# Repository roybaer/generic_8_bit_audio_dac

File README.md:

# Generic 8 bit audio DAC

These are KiCAD and Inkscape design files for a generic Covox Speech Thing compatible parallel port audio DAC.

This particular design uses a 100kΩ SIP R2R DAC with a 25.5kΩ load resistor and a pass-through connector for a printer and is therefore significantly closer to the original than most other imitations.

## Photo

## License

This work is licensed under the Creative Commons Attribution-ShareAlike 4.0 International License. To view a copy of this license, visit http://creativecommons.org/licenses/by-sa/4.0/ or send a letter to Creative Commons, PO Box 1866, Mountain View, CA 94042, USA.

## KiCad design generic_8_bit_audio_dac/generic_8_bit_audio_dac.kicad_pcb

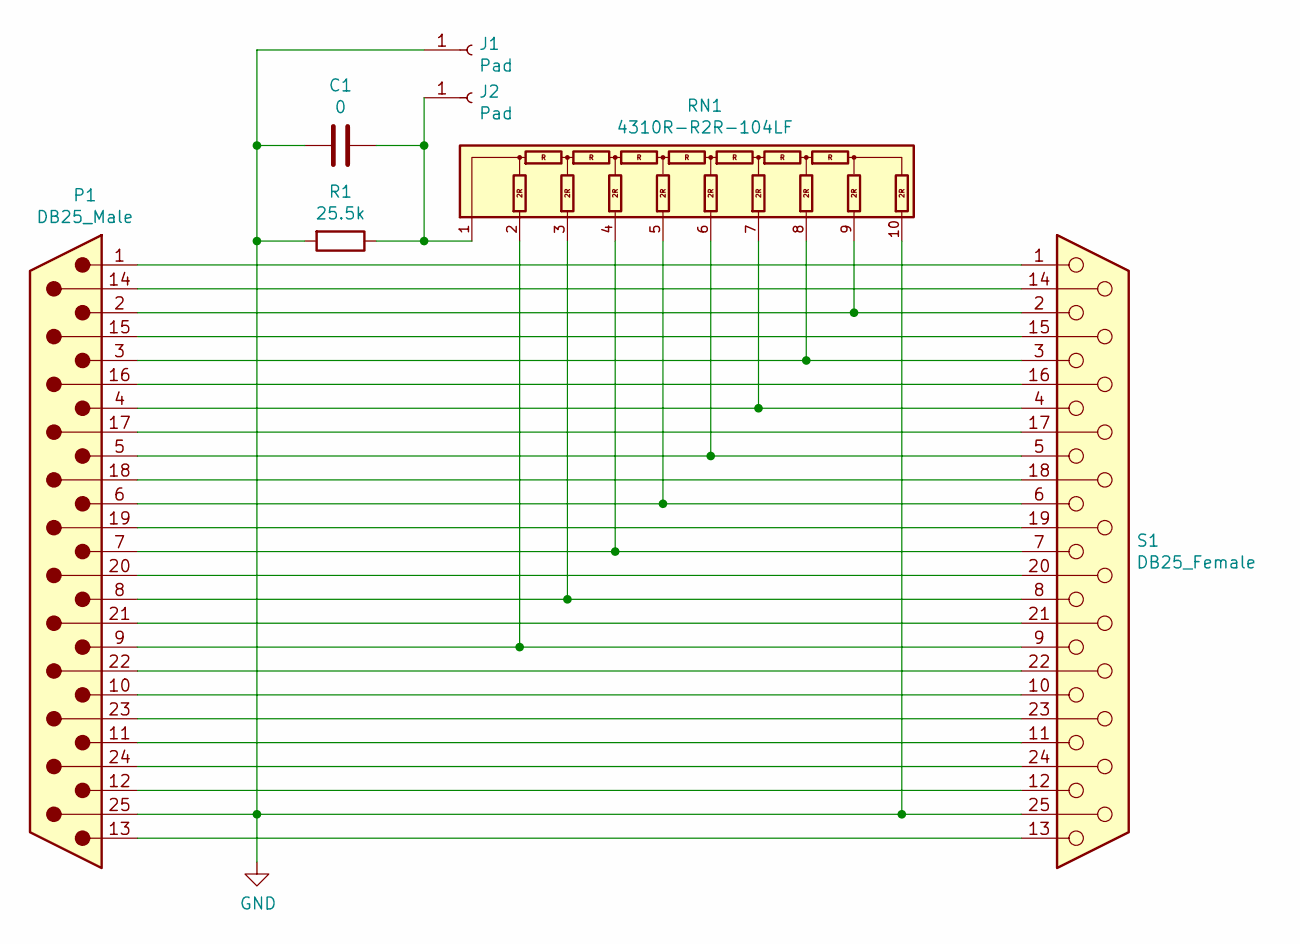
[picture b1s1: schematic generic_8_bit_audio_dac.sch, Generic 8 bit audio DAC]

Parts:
C1: 0; C_Disc_D4.7mm_W2.5mm_P5.00mm
J1, J2: Pad; SolderWirePad_1x01_Drill1.2mm
P1: DB25_Male; DSUB-25_Male_EdgeMount_P2.77mm
R1: 25.5k; R_Axial_DIN0309_L9.0mm_D3.2mm_P20.32mm_Horizontal
RN1: 4310R-R2R-104LF; R_Array_SIP10
S1: DB25_Female; DSUB-25_Female_EdgeMount_P2.77mm

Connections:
GND: C1.2, J1.1, P1.25, R1.2, RN1.10, S1.25
unnamed: C1.1, J2.1, R1.1, RN1.1
unnamed: P1.1, S1.1
unnamed: P1.2, RN1.9, S1.2
unnamed: P1.3, RN1.8, S1.3
unnamed: P1.4, RN1.7, S1.4
unnamed: P1.5, RN1.6, S1.5
unnamed: P1.6, RN1.5, S1.6
unnamed: P1.7, RN1.4, S1.7
unnamed: P1.8, RN1.3, S1.8
unnamed: P1.9, RN1.2, S1.9
unnamed: P1.10, S1.10
unnamed: P1.11, S1.11
unnamed: P1.12, S1.12
unnamed: P1.13, S1.13
unnamed: P1.14, S1.14
unnamed: P1.15, S1.15
unnamed: P1.16, S1.16
unnamed: P1.17, S1.17
unnamed: P1.18, S1.18
unnamed: P1.19, S1.19
unnamed: P1.20, S1.20
unnamed: P1.21, S1.21
unnamed: P1.22, S1.22
unnamed: P1.23, S1.23
unnamed: P1.24, S1.24

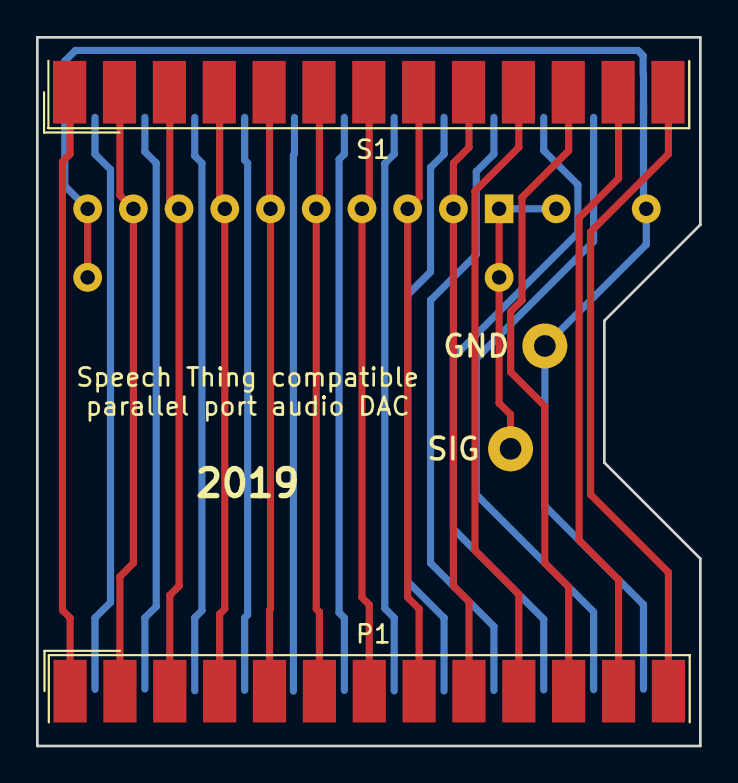
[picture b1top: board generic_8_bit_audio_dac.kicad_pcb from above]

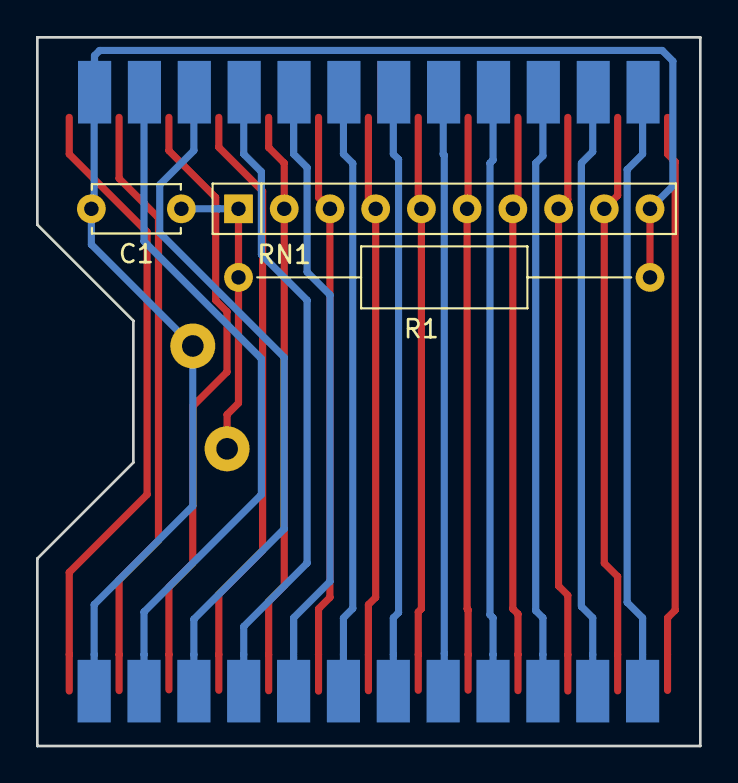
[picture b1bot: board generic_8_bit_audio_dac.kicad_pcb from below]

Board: 2 copper layers, 36.8 x 39.4 mm, 7 parts (3 on the bottom side), 26 nets.

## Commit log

2019-10-01 add KiCAD files
2019-10-01 add label (Inkscape SVG)
2019-10-01 add README.md
2019-10-01 add photo
2019-10-01 add PDF version of the label
